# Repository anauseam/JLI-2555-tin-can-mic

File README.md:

# JLI-2555-tin-can-mic

A unprofessional "Mid"-Fi mic using a JLI 2555, meant to be housed in a tin can.

## Specs

Output voltage is designed to output a commercial level line signal via a TS connection.

All the components were designed to be purely through hole and non-obsolete, thus limiting the choices drastically.

If you would like a circuit that you can order pre made refer to the [WIP] Repo.

## Notes / Known issues

Because the potentiometer is DC biased, when the potentiometer collects dust years down the road there will be a scratching nose when turning the knob. Given that this is a literal mic housed in a tin can, I can accept this fact

Yes the entire circuit is running off of a 9v. This makes things as simple as possible, perfect for a proof of concept tin can microphone. Reasons for the unipolar supply:

- Adding a bipolar supply (two batteries) would introduce a new array of issues (e.g. uneven battery drain, size)

The biggest issue (IMO) is the OPA134 itself. Although it does have an excellent noise floor compared to standard op amps, compared a something like the OPA1642, or a proper discrete JFET, it has a noise floor of about 12.45 nV/sqrt(Hz) when considering the op amp's voltage noise and the voltage noise from the affect of the op amp's current noise and 1G resistor.

## TODO

Current the PCB is haphazardly connected, a proper layout will be completed once testing of the original circuit is done.

I will probably create a proper pcb with SMT

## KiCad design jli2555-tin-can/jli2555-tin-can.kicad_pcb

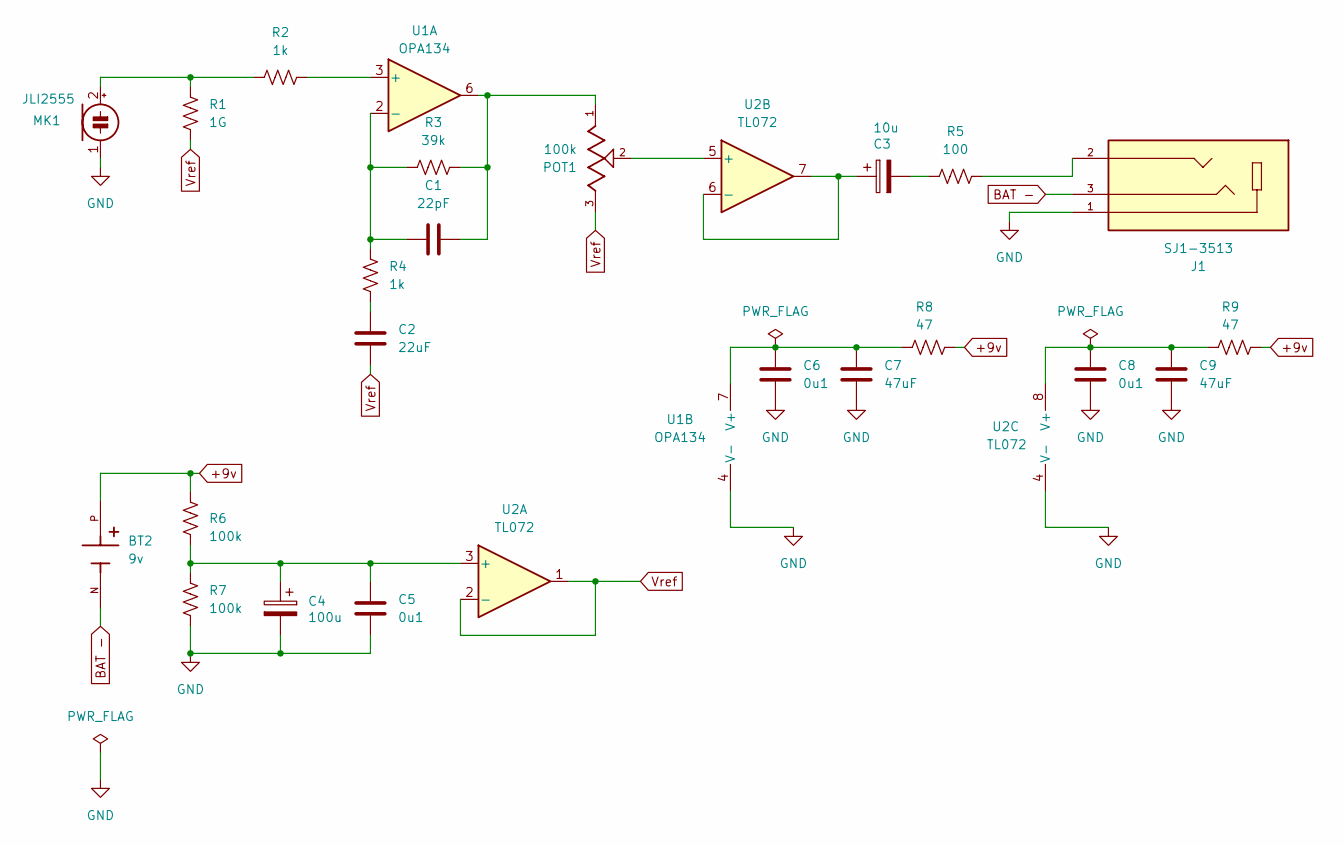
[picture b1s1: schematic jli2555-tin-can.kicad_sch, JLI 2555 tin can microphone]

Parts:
BT2: 9v; BAT_1294; PARTREV C
C1: 22pF; C_Disc_D5.0mm_W2.5mm_P2.50mm
C2: 22uF; C_Disc_D5.0mm_W2.5mm_P2.50mm
C3: 10u; CP_Radial_D5.0mm_P2.50mm
C4: 100u; CP_Radial_D6.3mm_P2.50mm
C5, C6, C8: 0u1; C_Disc_D5.0mm_W2.5mm_P2.50mm
C7, C9: 47uF; C_Disc_D5.0mm_W2.5mm_P2.50mm
J1: SJ1-3513; CUI_SJ1-3513; PARTREV 1.03
MK1: JLI2555; SolderWire-0.1sqmm_1x02_P3.6mm_D0.4mm_OD1mm
POT1: 100k; POT_PTN16-A100120K1A1; PARTREV 1.0
R1: 1G; R_Axial_DIN0207_L6.3mm_D2.5mm_P10.16mm_Horizontal
R2, R4: 1k; R_Axial_DIN0207_L6.3mm_D2.5mm_P10.16mm_Horizontal
R3: 39k; R_Axial_DIN0207_L6.3mm_D2.5mm_P10.16mm_Horizontal
R5: 100; R_Axial_DIN0207_L6.3mm_D2.5mm_P10.16mm_Horizontal
R6, R7: 100k; R_Axial_DIN0207_L6.3mm_D2.5mm_P10.16mm_Horizontal
R8, R9: 47; R_Axial_DIN0207_L6.3mm_D2.5mm_P10.16mm_Horizontal
U1: OPA134; DIP-8_W7.62mm_Socket
U2: TL072; DIP-8_W7.62mm_Socket

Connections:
+9v: BT2.P, R6.1, R8.2, R9.2
BAT -: BT2.N, J1.3
GND: C4.2, C5.1, C6.1, C7.1, C8.1, C9.1, J1.1, MK1.1 (-), R7.2, U1.4 (V-), U2.4 (V-)
unnamed: C1.2, POT1.1, R3.2, U1.6
unnamed: C2.2, R4.2
unnamed: C3.2, R5.1
unnamed: J1.2, R5.2
unnamed: MK1.2 (+), R1.1, R2.1
unnamed: R2.2, U1.3 (+)
unnamed: C1.1, R3.1, R4.1, U1.2 (-)
unnamed: C6.2, C7.2, R8.1, U1.7 (V+)
unnamed: C4.1, C5.2, R6.2, R7.1, U2.3 (+)
unnamed: POT1.2, U2.5 (+)
unnamed: C3.1, U2.6 (-), U2.7
unnamed: C8.2, C9.2, R9.1, U2.8 (V+)
Vref: C2.1, POT1.3, R1.2, U2.1, U2.2 (-)

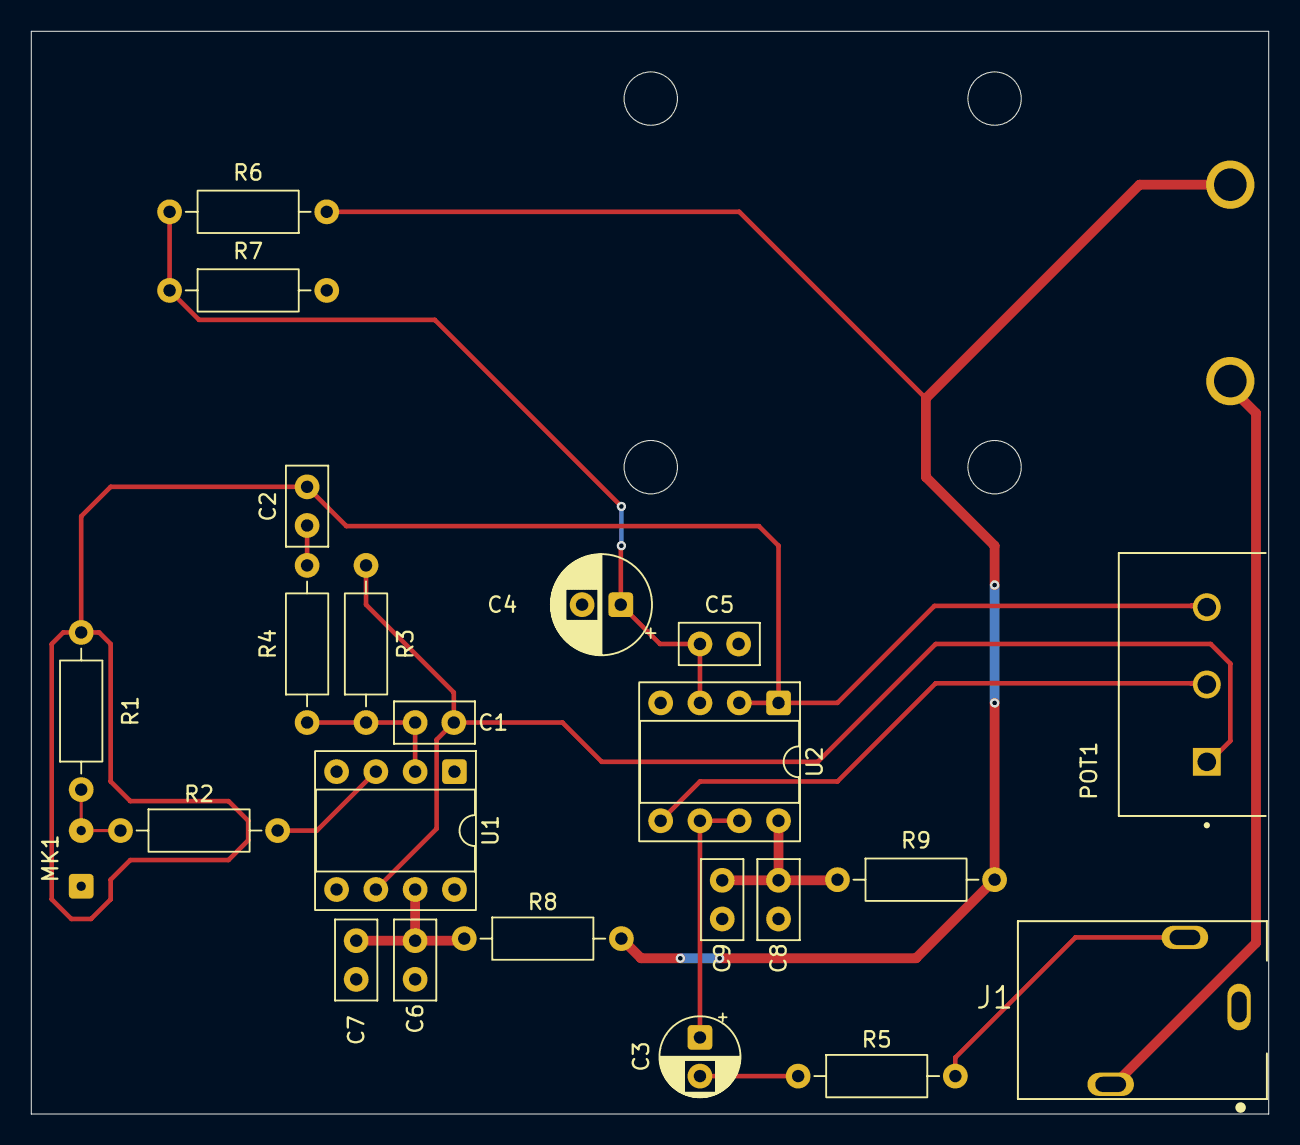
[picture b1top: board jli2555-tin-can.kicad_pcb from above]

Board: 2 copper layers, 80.0 x 70.0 mm, 24 parts (1 on the bottom side), 16 nets.

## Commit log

2025-11-25 finalize the -9v powered circuit design. Renamed entire project
2025-11-26 Finalization of the first printed prototype, revision 1
2025-11-26 Update zip
2025-11-27 add circuit image to readme
